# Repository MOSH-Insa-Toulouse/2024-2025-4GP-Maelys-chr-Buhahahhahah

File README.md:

# 2024-2025-4GP-Maelys-chr-Buhahahhahah

## Sommaire

1. [Présentation du projet](#présentation-du-projet)  
2. [Livrables](#livrables)  
3. [Matériel nécessaire](#matériel-nécessaire)  
4. [Simulation du circuit électronique sous LTspice](#simulation-du-circuit-électronique-sous-ltspice)  
5. [Création de notre PCB sous KiCad](#création-de-notre-pcb-sous-kicad)
6. [Fabrication du shield](#fabrication-du-shield)
7. [Programme Arduino](#programme-arduino)  
8. [Application Android APK sous MIT App Inventor](#application-android-apk-sous-mit-app-inventor)   
9. [Banc de test](#banc-de-test)   
10. [Datasheet](#datasheet)  
11. [Conclusion](#conclusion)  
12. [Contacts](#contacts)

## 1. Présentation du projet
Ce projet s’inscrit dans le cadre de l’Unité de Formation « Du capteur au banc de test » du département Génie Physique de l’INSA Toulouse. Inspiré de l’article "Pencil Drawn Strain Gauges and Chemiresistor on Paper", publié en 2014 dans Scientific Reports, l’objectif est de concevoir un capteur de déformation low-tech à base de papier et de graphite. 

Le principe repose sur le fait que, lors d’une déformation du papier, la distance entre les particules de graphite préalablement déposées varie selon qu’il s’agisse d’une tension ou d’une compression. Cette variation entraîne une modification de la conductivité, et donc de la résistance électrique de la couche de graphite. Il est ainsi possible de mesurer cette variation de résistance pour en déduire la déformation appliquée. L’objectif du projet était de concevoir ce capteur dans son intégralité, en suivant toutes les étapes de développement : du design et de la fabrication du circuit imprimé (PCB), jusqu’à la programmation et aux tests du capteur.

## 2. Livrables
Pour ce projet, nous avions différents livrables à rendre : 

- Un shield PCB fonctionnel connecté à une carte Arduino UNO. Notre PCB contient un amplificateur transimpédance, un capteur bluetooth, un écran OLED. Ainsi qu'un flex sensor, un servo moteur, un potentiomètre digital et un encodeur rotatoir. Nous avons également rajouté une led de couleur bleu. 
- Un code Arduino permettant de gérer le module bluetooth ainsi que les mesures du capteur de déformation et nos différents composants présent sur notre PCB.
- Une application Android APK développée à l’aide du site MIT app inventor.
- Un Banc de test que nous avons fabriqué
- Une datasheet du capteur de contrainte

## 3. Matériel nécessaire
- Résistances : 1 de 1 kOhms, 1 de 10 kOhms, 2 de 100 kOhms pour l'amplificateur transimpédance. 1 de 320 Ohms pour la Led et 1 de 10 kOhms pour le flex sensor
- Capacités : 2 de 100 nF, 1 de 1 uF pour l'amplificateur transimpédance.
- Arduino Uno
- Amplificateur opérationnel LTC1050
- Module Bluetooth HC05
- Encodeur rotatoire 
- Ecran OLED 128x64
- Potientomètre digital MCP41050
- Flex Sensor
- Servo moteur
- Led
  
## 4. Simulation du circuit électronique sous LTSpice
Ce dossier contient le schéma du circuit analogique associé au capteur graphite. Celui-ci intègre un amplificateur transimpédance ainsi que plusieurs filtres passe-bas, permettant d’obtenir un signal exploitable par la suite.

Le capteur délivre un courant très faible, de l’ordre de 100 nA en moyenne. Sans traitement, ce signal serait difficile à exploiter. L’amplificateur permet donc de convertir ce courant en une tension mesurable, tandis que les filtres atténuent les perturbations indésirables.

Les interférences à 50 Hz, liées au réseau électrique, ainsi que d’autres parasites (bruits de l’alimentation, de l’horloge, etc.) peuvent fortement impacter la qualité du signal. C’est pourquoi un filtrage soigneux est nécessaire.

### Choix de l’amplificateur
Nous avons choisi l’amplificateur opérationnel (AOP) LTC1050 car il est spécifiquement conçu pour traiter de très faibles courants d’entrée. Son offset de tension très faible garantit une grande précision dans la conversion courant/tension.

### Les filtres
Trois filtres ont été intégrés au circuit :

- 🟨 Rectangle jaune : simulation du capteur  
- 🟧 Rectangle orange + R5 : simulation du bruit 

Et trois autres filtres, visibles sur le schéma, assurent le nettoyage du signal :

- 🟩 Filtre en entrée (R1, C1 – vert) : filtre passe-bas passif, fréquence de coupure ≈ 16 Hz, pour atténuer les bruits en courant dès l’entrée du signal.  
- 🟥 Filtre dans la boucle AOP (R3, C4 – rouge) : filtre passe-bas, fréquence de coupure ≈ 1,6 Hz, efficace contre les interférences à 50 Hz du réseau électrique.  
- 🟪 Filtre en sortie (R6, C2 – violet) : filtre passe-bas passif avec une fréquence de coupure d’environ 1,6 kHz, pour éliminer les parasites générés lors du traitement du signal.

### Schéma de simulation

## 5. Conception de notre PCB sous Kicad
Cette étape du projet avait pour objectif de concevoir le PCB du circuit transimpédance à l’aide du logiciel KiCad, en s’appuyant sur un template de carte Arduino Uno. Plusieurs étapes ont été nécessaires :

- **Création de la schématique** du circuit transimpédance, incluant la définition de symboles personnalisés pour les composants absents de la bibliothèque KiCad.
- **Conception des empreintes physiques** de ces composants, en prenant en compte leurs caractéristiques techniques : nombre de pins, espacement, dimensions, géométrie, etc.
- **Routage du circuit** généré via la vue schématique.
- **Mise en place d’un plan de masse** pour relier efficacement les pistes au GND.

Voici le schéma électrique de l'ensemble de notre montage :

Nous avons conçu les empreintes physiques de nos composants afin de pouvoir les positionner correctement sur le PCB et nous avons fait le routage.
La principale difficulté rencontrée a été d’optimiser le placement des composants afin d’éviter l’utilisation de vias, notamment pour les connexions au plan de masse (GND).
Objectif réussi nous avons utilisé 0 via !

Voici le résultat final obtenu de notre routage :
<br/><br/>

Voici la version 3D : 

### ⚠️ Remarques importantes pour les futurs étudiants !!!

Au cours de notre projet, nous avons rencontré plusieurs erreurs qu’il est important de signaler afin d’éviter qu’elles ne se reproduisent :

- **Encodeur rotatoire** :  
  Le modèle présent dans KiCad ne correspondait pas exactement au composant réel que nous avons utilisé. Il a donc été nécessaire d'interchanger les connexions des broches Switch et Clock.

- **Servomoteur** :  
  Les broches GND et 5V étaient inversées par rapport au modèle. Nous avons résolu ce problème en utilisant un connecteur permettant de corriger le câblage.

- **Potentiomètre numérique** :  
  La broche CS (Chip Select) doit être connectée à la pin 10 de l’Arduino, et non à la pin 12, cette dernière étant utilisée par la bibliothèque SPI n'est pas disponile.

- **Entrée de l’amplificateur opérationnel** :  
  Les entrées **+** et **–** de l’AOP ont été inversées par erreur. Il est important de bien vérifier leur affectation dans le schéma et lors du câblage.

## 6. Fabrication du shield 
Grâce à notre projet réalisé sous KiCad, nous avons pu générer le masque de gravure de notre PCB. Nous avons ensuite transmis notre fichier à Cathy, qui s’est chargée de l’impression et de la fabrication du circuit.

Elle a procédé ainsi :

1. Impression du calque de la PCB
2. Insolation UV d’une plaque en époxy recouverte d’une fine couche de cuivre et d’une résine photosensible.
3. Développement de la plaque dans un révélateur pour éliminer la résine non exposée.
4. Gravure des pistes dans un bain de perchlorure de fer, afin de retirer le cuivre non protégé.
5. Nettoyage final à l’acétone pour enlever les résidus de résine restants.

Un grand merci à Cathy pour le temps qu’elle a consacré à la fabrication de notre PCB!

### Assemblage du circuit
Nous avons ensuite réalisé le perçage de la plaquette afin de pouvoir y insérer les différents composants selon le schéma généré avec KiCad.  
Une fois le perçage terminé, nous avons procédé à la soudure des composants sur la carte, en respectant le plan de câblage.

## 7. Programme Arduino 
Notre code contient les instructions nécessaires au bon fonctionnement de l’Arduino.  
Il permet de traiter les données reçues du capteur graphite et de les transmettre au module Bluetooth HC-05, qui communique avec l’application APK. Il gère également l’interaction avec le potentiomètre digital ainsi qu’avec l’écran OLED. De plus au niveau de notre code Arduino, il prend 10 mesures à la fois et envoie une moyenne arithmétique, le bruit à donc moins d'impact. 
Plusieurs bibliothèques sont intégrées pour faciliter ces communications :

- **Adafruit_SSD1306** : simplifie l’affichage des informations sur l’écran OLED  
- **SPI** : permet de communiquer les nouvelles valeurs sur le potentiomètre digital
- **SoftwareSerial** : permet la communication avec le module Bluetooth HC-05  

Nous avons conçu un menu interactif composé de 4 options, accessible via l'encodeur rotatoire. Celui-ci permet de naviguer entre les différentes options, et une simple pression sur le bouton intégré permet de sélectionner et activer l’option souhaitée. 

Voici notre menu : 

1. **Configuration du capteur graphite**
   - Met à jour la valeur du potentiomètre digital
   - Récupère la résistance à plat (R₀)
   - Transmet les données à l’application via Bluetooth

2. **Configuration du capteur flex sensor**
   - Récupère la valeur de la résistance de référence (R₀)
   - Transmet les données à l’application via Bluetooth

3. **Mesure du capteur graphite**
   - Envoie des données ponctuelles du capteur graphite
   - Les données sont reçues par l’application et enregistrées dans un fichier texte

4. **Mesure du capteur flex sensor**
   - Envoie des données ponctuelles du capteur flex
   - Les données sont également reçues par l’application et sauvegardées dans un fichier texte
  
## 8. Application Android APK sous MIT App Inventor
Nous avons développé une application Android à l’aide de la plateforme MIT App Inventor. Cette application permet de recevoir les données envoyées par la carte Arduino via une connexion Bluetooth, établie grâce au module HC-05 intégré au shield de la carte.

Une fois la connexion Bluetooth établie, l’application après chaque mesure affiche:

- Un **graphe dynamique** représentant l’évolution de la résistance du capteur graphite et du capteur flex en fonction et des contraintes appliquées.
- La **valeur instantanée** de cette résistance.

L'algorithme d'utilisation étant le suivant : 
  1) A l'aide de l'encodeur rotatoire naviguer vers "Conf. CG" ou "Conf. Flex" en fonction de ce que vous avez besoin de mésurer, puis appuyer sur l'encodeur
  2) Naviguer vers "Mes. CG" ou "Mes. Flex", et appuyer sur l'encodeur quand le capteur sera positionné sous la contrainte souhaité (initialement ça a été conçu pour notre banc de test, de 10mm à 22.5mm de rayon de courbure)
  3) Appuyer encore plusieurs fois (tant que le led bleu est allumée)
  4) Récuperer le fichier dans la destination Documents/MOSH/ de votre téléphone
     
Voici notre application : 
<br/><br/>
## 9. Banc de test
Afin de spécifier le comportement de notre capteur graphite avec son montage transimpédance, avec le binôme de Tristan et Yannis nous avons conçu et fabriqué notre propre banc de test au FabLab de l’INSA.

Ce dispositif se compose de demis-cercles de diamètres différents avec des trous préfabriqués, permettant d’insérer facilement le capteur. Une fois placé dans l’un des trous, le capteur épouse la courbure du demi-cercle correspondant. Cette contrainte appliquée provoque une variation de sa résistance électrique, que nous mesurons.

Ces demi-cercles, utilisés pour appliquer une contrainte progressive sur le capteur, présentent les caractéristiques suivantes :

- Diamètre du plus petit demi-cercle : 20 mm
- Diamètre du plus grand demi-cercle : 45 mm
- Incrément entre chaque modèle : 5 mm

Ce montage nous permet de relier la déformation mécanique :
ε = e / D

à la variation relative de la résistance :
ΔR / R₀

où :
- e = 0,2 mm correspond à l’épaisseur du papier conducteur utilisé
- D est le diamètre du demi-cercle sélectionné

Voici notre banc de test avec ses dimensions : 

Nous avons ensuite tracé les courbes caractéristiques obtenues pour des crayons de duretés différentes (3B,HB et H) en situation de tension ou de compression, afin d’évaluer la réponse du capteur.

En théorie, lorsque le capteur est soumis en tension, la monocouche de graphite déposée sur le papier s’étire, ce qui augmente la distance entre les atomes de carbone. Cette augmentation de distance entraîne une hausse de la résistance du capteur. À l’inverse, lorsqu’il est soumis à une compression, les atomes de carbone se rapprochent, ce qui réduit la résistance du capteur. La variation relative de résistance dépend également du type de crayon utilisé pour tracer la couche de graphite. Plus le crayon est gras (par exemple, du H vers le HB jusqu’au 3B, qui contient le plus de carbone), plus la variation relative de résistance est faible. Bien que la théorie prévoie une augmentation de la résistance en tension et une diminution en compression, nos résultats expérimentaux ne suivent pas totalement cette tendance attendue :

#### Compression  
Sur la courbe de compression, on observe bien une diminution de la résistance relative (ΔR / R₀) lorsque la déformation augmente.  
En revanche, le graphite 3B, censé avoir une plus faible variation relative en théorie (car moins conducteur), présente ici la plus grande variation de résistance.

#### Extension  
En tension, les résultats montrent bien une augmentation de la résistance avec la déformation. Cependant, contrairement à la théorie, le crayon HB présente ici la variation la plus élevée, suivi du H, tandis que le 3B varie beaucoup moins. Cela contredit l’idée selon laquelle les crayons les plus dures (ici H) varient le plus.

#### Interprétation 
En effet, plusieurs facteurs influencent le comportement réel du capteur :
- L’uniformité du dépôt de graphite sur le capteur.
- La qualité des crayons 
- Le contact électrique entre le graphite et les pinces.

### Comparaison entre le capteur graphite et le capteur Flex sensor commercial

Nous avons comparé les performances de notre capteur graphite artisanal à un capteur flex commercial. La comparaison s’appuie sur les résultats expérimentaux obtenus en extension :

Les courbes montrent que le flex sensor présente une variation relative de résistance nettement plus marquée que nos capteurs en graphite.

- **Capteur Flex sensor** : pente ≈ **237,36**
- **Capteur graphite HB** : pente ≈ **43,5**
- **Capteur graphite H** : pente ≈ **34,6**
- **Capteur graphite 3B** : pente ≈ **20,3**

Le capteur Flex est donc beaucoup plus sensible à la déformation. Sa réponse est plus régulière, linéaire et plus exploitable en conditions réelles.

## Datasheet 
Vous pouvez consulter la datasheet de notre capteur [ici](./Datasheet.pdf)
## Conclusion
Industrialisation du capteur graphite – Est-ce envisageable ?

- Le **capteur graphite** est une solution low-cost. Toutefois, il reste moins précis, plus bruité et moins robuste face aux manipulations répétée. Cependant, il présente des avantages important comme le fait de pouvoir choisir la forme du capteur ainsi que la manière dont on souhaite déposer le graphite. Grâce à notre capteur on peut mesurer la variation de la resistance en fonction de la tension et de la compression. 
- Le **flex sensor** offre une très bonne sensibilité, une meilleure fiabilité, et une stabilité supérieure sur le long terme. Il est donc plus adapté aux applications industrielles, même si son coût est plus élevé. Cependant, le flex sensor permet de mesurer la variation de la résistance que en fonction de la tension. 

Notre capteur graphite remplit bien son rôle dans le cadre d’une expérimentation à faible coût, mais reste limité pour des usages où la précision et la répétabilité sont essentielles.

### Vers une industrialisation possible : pistes d'amélioration

Bien que notre capteur graphite artisanal ne soit pas directement industrialisable, plusieurs pistes d’amélioration permettraient d’envisager une version plus robuste, homogène et durable, adaptée à une production en série.

#### Structure et matériaux

- Remplacer le papier par un support plastique souple permettrait d’augmenter considérablement la durée de vie du capteur.
- Alternativement, le papier peut être traité ou plastifié, afin de le protéger de l’humidité et des dégradations mécaniques tout en conservant sa flexibilité.
- Encapsuler le capteur entre deux couches de plastique le protégerait des frottements, de la poussière et de l’humidité.

#### Dépôt du graphite

- Pour garantir une bonne homogénéité et une reproductibilité industrielle :
  - Saturer la zone sensible en graphite, en déposant une grande quantité de matière,
  - Utiliser des motifs de colle comme guide, puis saupoudrer de la poudre de graphite,
  - Fixer la couche de graphite de manière durable, pour éviter qu’elle ne s'efface ou se dégrade avec le temps.

#### Connectique

- En remplaçant les pinces crocos par des plaques métalliques conductrices insérées entre les deux couches de plastique, on obtiendrait une connexion plus fiable.
- Ce système permettrait également une meilleure intégration dans des circuits électroniques.

#### Bénéfices attendus

Ces améliorations permettraient :
- Une meilleure homogénéité du comportement du capteur,
- Une réduction de la sensibilité aux conditions environnementales (humidité, poussière, frottements),
- Une durée de vie allongée,
- Une intégration facilitée dans des applications à bas coût ou semi-industrielles.

## Contacts

Pour toutes questions éventuelles vous pouvez nous contacter par mail : 
- Artur Nersisyan : nersisya@insa-toulouse.fr
- Maelys Christien : christien@insa-toulouse.fr

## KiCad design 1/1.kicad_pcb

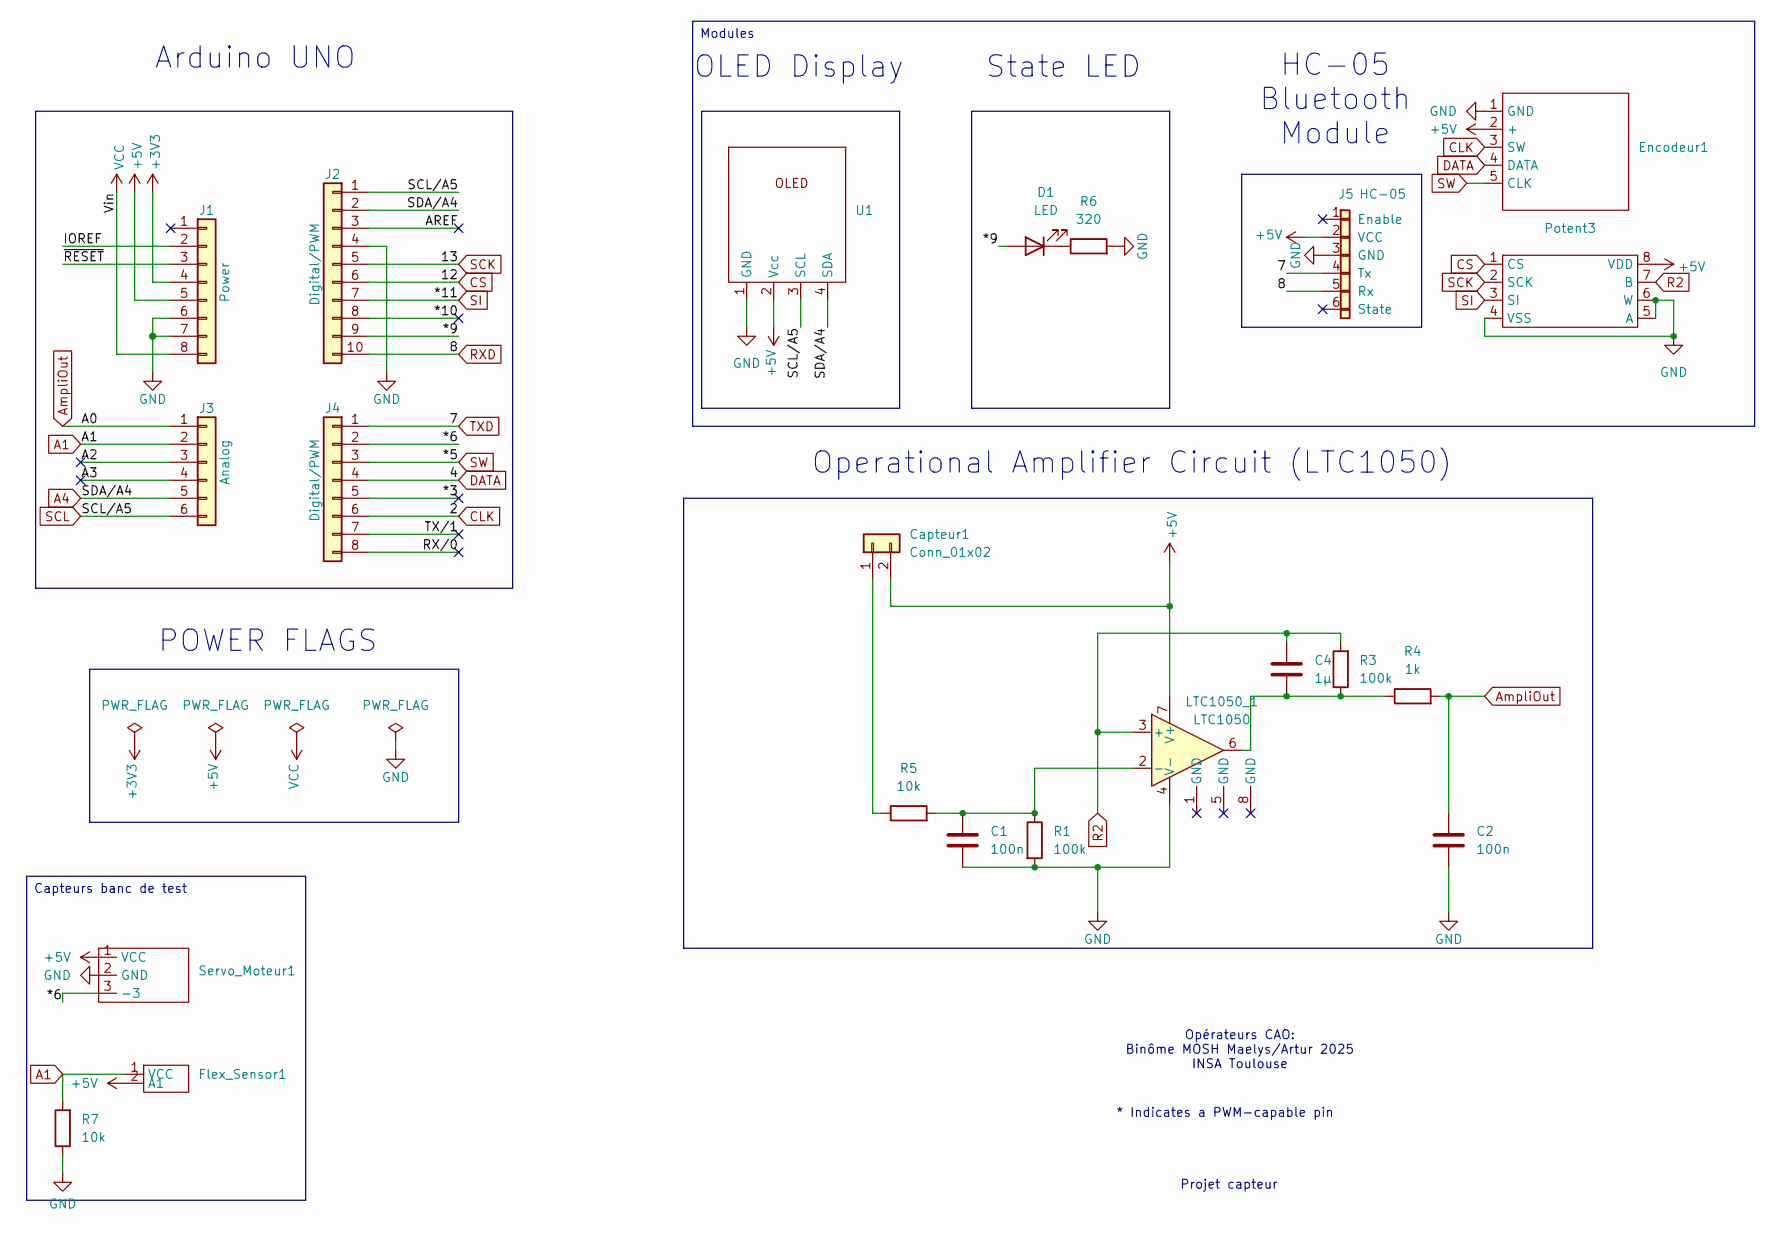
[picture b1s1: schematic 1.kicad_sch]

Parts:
C1, C2: 100n; C_Disc_D9.0mm_W5.0mm_P5.00mm
C4: 1µ; C_Rect_L9.0mm_W6.4mm_P7.50mm_MKT
Capteur1: Conn_01x02; PinSocket_1x02_P2.54mm_Vertical
D1: LED; LED_D5.0mm
Encodeur1: Encodeur
Flex_Sensor1: flex_sensor
J1: Power; PinSocket_1x08_P2.54mm_Vertical
J2: Digital/PWM; PinSocket_1x10_P2.54mm_Vertical
J3: Analog; PinSocket_1x06_P2.54mm_Vertical
J4: Digital/PWM; PinSocket_1x08_P2.54mm_Vertical
J5: HC-05; HC-05_footprint
LTC1050_1: LTC1050; DIP-8_W7.62mm
Potent3: potentiometre_digit
R1, R3: 100k; R_Axial_DIN0207_L6.3mm_D2.5mm_P10.16mm_Horizontal
R4: 1k; R_Axial_DIN0207_L6.3mm_D2.5mm_P10.16mm_Horizontal
R5, R7: 10k; R_Axial_DIN0207_L6.3mm_D2.5mm_P10.16mm_Horizontal
R6: 320; R_Axial_DIN0207_L6.3mm_D2.5mm_P10.16mm_Horizontal
Servo_Moteur1: servo
U1: OLED1306

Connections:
+3V3: J1.4
+5V: Capteur1.2, Encodeur1.2 (+), Flex_Sensor1.2 (A1), J1.5, J5.2 (VCC), LTC1050_1.7 (V+), Potent3.8 (VDD), Servo_Moteur1.1 (VCC), U1.2 (Vcc)
/*3: J4.5
/*6: J4.2, Servo_Moteur1.3 (-3)
/*9: D1.2 (A), J2.9
/*10: J2.8
/A2: J3.3
/A3: J3.4
/AREF: J2.3
/IOREF: J1.2
/RX/0: J4.8
/TX/1: J4.7
/~RESET: J1.3
A1: Flex_Sensor1.1 (VCC), J3.2, R7.2
A4: J2.2, J3.5, U1.4 (SDA)
AmpliOut: C2.2, J3.1, R4.2
CLK: Encodeur1.3 (SW), J4.6
CS: J2.6, Potent3.1 (CS)
DATA: Encodeur1.4 (DATA), J4.4
GND: C1.1, C2.1, Encodeur1.1 (GND), J1.6, J1.7, J2.4, J5.3 (GND), LTC1050_1.4 (V-), Potent3.4 (VSS), Potent3.5 (A), Potent3.6 (W), R1.2, R6.2, R7.1, Servo_Moteur1.2 (GND), U1.1 (GND)
unnamed: C4.1, LTC1050_1.6, R3.1, R4.1
unnamed: Capteur1.1, R5.1
unnamed: D1.1 (K), R6.1
unnamed: C1.2, LTC1050_1.2 (-), R1.1, R5.2
R2: C4.2, LTC1050_1.3 (+), Potent3.7 (B), R3.2
RXD: J2.10, J5.5 (Rx)
SCK: J2.5, Potent3.2 (SCK)
SCL: J2.1, J3.6, U1.3 (SCL)
SI: J2.7, Potent3.3 (SI)
SW: Encodeur1.5 (CLK), J4.3
TXD: J4.1, J5.4 (Tx)
VCC: J1.8

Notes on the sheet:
Opérateurs CAO: Binôme MOSH Maelys/Artur 2025 INSA Toulouse
POWER FLAGS
HC-05 Bluetooth Module
Arduino UNO
Operational Amplifier Circuit (LTC1050)
OLED Display
Projet capteur
* Indicates a PWM-capable pin
State LED
Capteurs banc de test
Modules

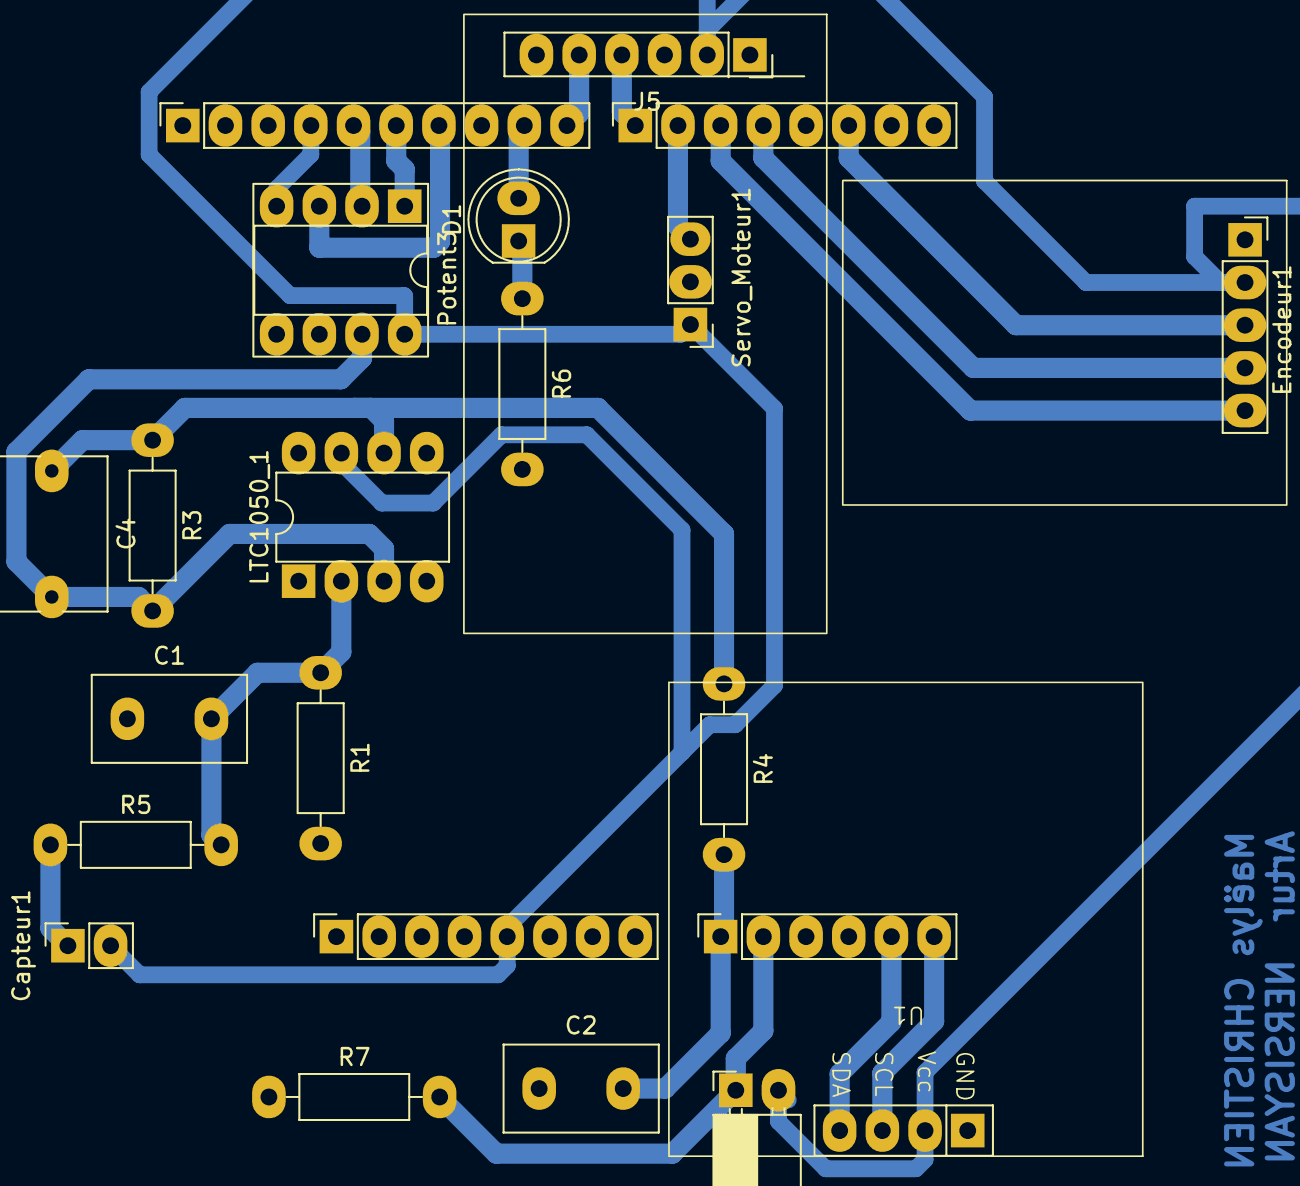
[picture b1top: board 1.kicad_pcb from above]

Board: 2 copper layers, 22 parts (0 on the bottom side), 21 nets.

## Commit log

2025-03-16 Remove duplicated directory
2025-03-16 First update of readme
2025-03-16 The first version of our shield BEFORE rooting
2025-03-18 Modifactions on kicad project and ltspice are added
2025-03-18 Rajout des capteurs
2025-03-18 mise à jour bib
2025-03-18 Face avant v1
2025-03-18 MAJ de la face arrière avant la routage
2025-03-18 Rootage v1
2025-03-23 Fichiers gerbers ajoutées
2025-03-25 V2 de routage de la carte
2025-03-25 Routage V3
2025-03-25 Routage V3 + noms + 3D models
2025-04-06 Create image
2025-04-06 Rename lt spice.JPG to lt_spice.JPG
2025-04-06 Rename Capture d’écran 2025-04-06 à 21.02.01.png to schémacomplet.png
2025-04-07 Update README.md
    La taille de l'image de routage modifiée
2025-04-15 maj de PCB et de code et l'application arduino ajouté
2025-04-15 maj de photo de 3D de pcb
2025-04-15 MAJ README.md
